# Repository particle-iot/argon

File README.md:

# Argon

<div align=center></div>

### Overview

The Argon is a powerful Wi-Fi enabled development board that can act as either a standalone Wi-Fi endpoint or Wi-Fi enabled gateway for Particle Mesh networks. It is based on the Nordic nRF52840 and has built-in battery charging circuitry so it’s easy to connect a Li-Po and deploy your local network in minutes.

The Argon is great for connecting existing projects to the Particle Device Cloud or as a gateway to connect an entire group of local endpoints.

### Features

* Espressif ESP32-D0WD 2.4Ghz Wi-Fi coprocessor 
  * On-board 4MB flash for ESP32 
  * 802.11 b/g/n support 
  * 802.11 n (2.4 GHz), up to 150 Mbps
* Nordic Semiconductor nRF52840 SoC 
  * ARM Cortex-M4F 32-bit processor @ 64MHz 
  * 1MB flash, 256KB RAM 
  * IEEE 802.15.4-2006: 250 Kbps 
  * Bluetooth 5: 2 Mbps, 1 Mbps, 500 Kbps, 125 Kbps 
  * Supports DSP instructions, HW accelerated Floating Point Unit (FPU) calculations 
  * ARM TrustZone CryptoCell-310 Cryptographic and security module 
  * Up to +8 dBm TX power (down to -20 dBm in 4 dB steps) 
  * NFC-A tag
* On-board additional 2MB SPI flash
* 20 mixed signal GPIO (6 x Analog, 8 x PWM), UART, I2C, SPI
* Micro USB 2.0 full speed (12 Mbps)
* Integrated Li-Po charging and battery connector
* JTAG (SWD) Connector
* RGB status LED
* Reset and Mode buttons
* On-board PCB antenna
* u.FL connector for external antenna
* Meets the Adafruit Feather [specification](https://learn.adafruit.com/adafruit-feather/feather-specification) in dimensions and pinout
* FCC, CE and IC certified
* RoHS compliant (lead-free)

### Structure of this repository:
 - /eagle
     + Contains the schematic and PCB files in the Eagle file format
 - /gerbers
     + Contains the manufacturing gerber files for the board
 - /datasheets
     + Contains the relevant datasheets of the components used on the Argon
 - /pdfs
     + Contains schematic files in PDF 

### Hardware datasheet

The complete datasheet for the Argon is available [here.](https://docs.particle.io/datasheets/wi-fi/argon-datasheet/)

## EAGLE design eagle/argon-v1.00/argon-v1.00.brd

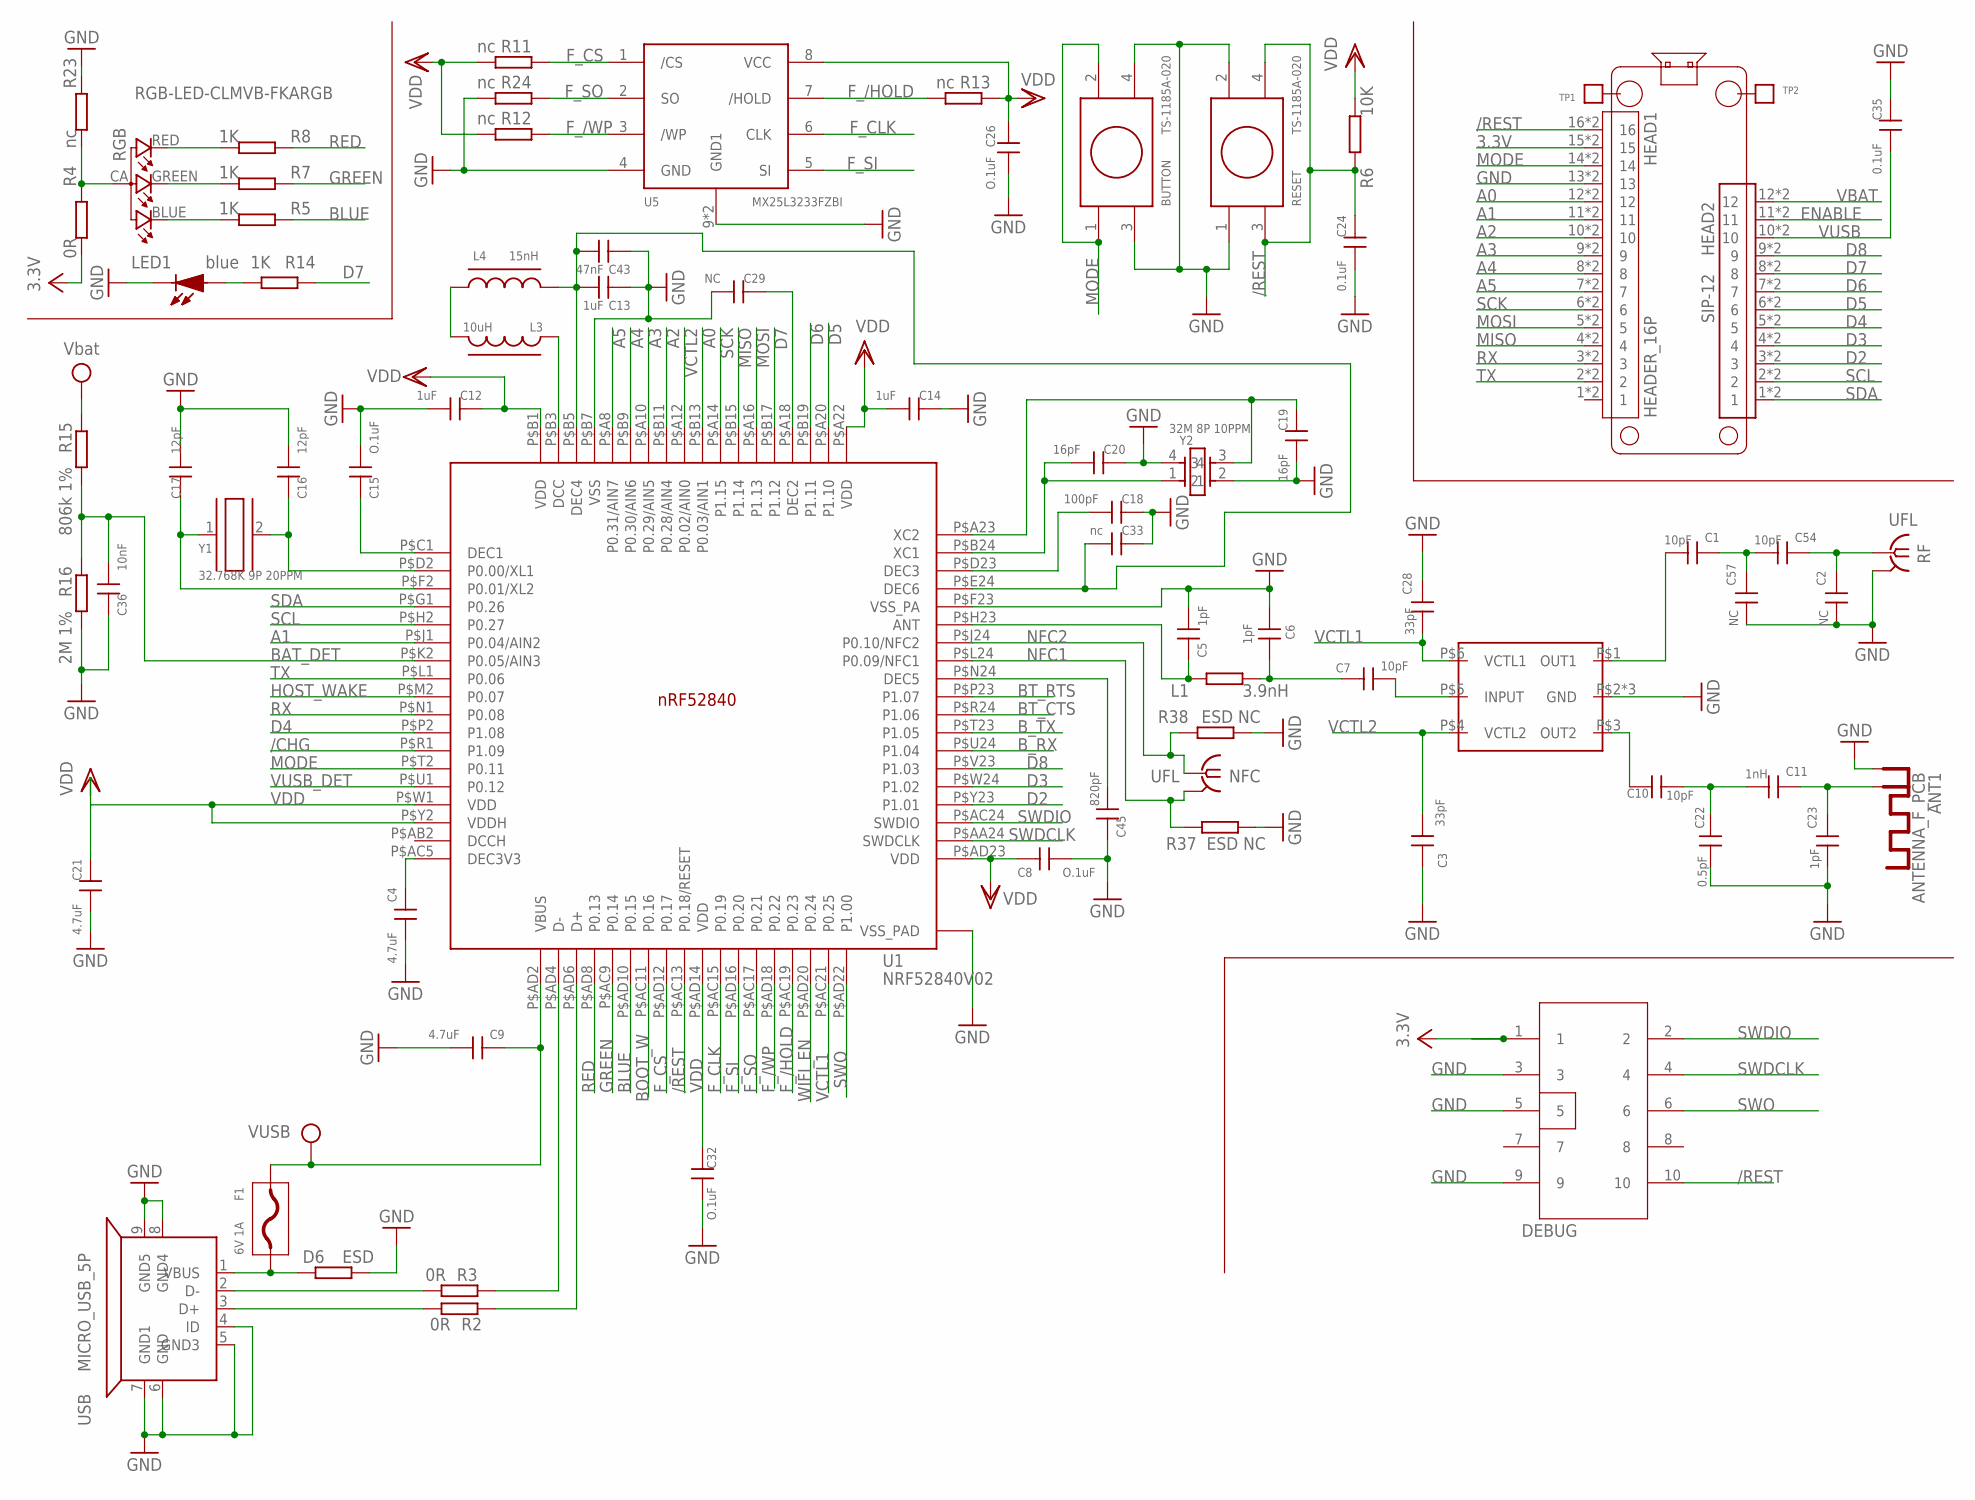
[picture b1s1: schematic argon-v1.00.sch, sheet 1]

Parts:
ANT1: ANTENNA_F_PCB
BUTTON: TS-1185A-020
C1, C7, C10, C54: 10pF; C-0402
C2, C29, C57: NC; C-0402
C3, C28: 33pF; C-0402
C4, C9, C21: 4.7uF; C-0402
C5, C6, C23: 1pF; C-0402
C8, C15, C26, C32: O.1uF; C-0402
C11: 1nH; C-0402
C12, C13, C14: 1uF; C-0402
C16, C17: 12pF; C-0402
C18: 100pF; C-0402
C19, C20: 16pF; C-0402
C22: 0.5pF; C-0402
C24, C35: 0.1uF; C-0402
C33: nc; C-0402
C36: 10nF; C-0402
C43: 47nF; C-0402
C45: 820pF; C-0402
D6: ESD; R-0402S
DEBUG: CON5X2; CON5X2_1.27
F1: 6V 1A; F0805
HEAD1: HEADER_16P; HEADER_16P2.54
HEAD2: SIP-12
L1: 3.9nH; R-0402S
L3: 10uH; R-0603A
L4: 15nH; R-0402S
LED1: blue; LED0603
NFC: UFL; IPEX-20279-001E
R2, R3, R4: 0R; R-0402S
R5, R7, R8, R14: 1K; R-0402S
R6: 10K; R-0402S
R11, R12, R13, R23, R24: nc; R-0402S
R15: 806k 1%; R-0402S
R16: 2M 1%; R-0402S
R37, R38: ESD NC; R-0402S
RESET: TS-1185A-020
RF: UFL; IPEX-20279-001E
RGB: RGB-LED-CLMVB-FKARGB; PLCC4-2MM-RGB
TP1, TP2: TPTP2.5; TP-2.5
U1: NRF52840V02; AQN507X7X0.85_HA-74_V2
U5: MX25L3233FZBI; USON8-3X4
U$2: SKY13351-378LF; MLPD-6-1X1
USB: MICRO_USB_5P; MICRO_USB
Y1: 32.768K 9P 20PPM; CRY_3215
Y2: 32M 8P 10PPM; CRY_2520

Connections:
3.3V: DEBUG.1, HEAD1.15, HEAD1.P$15 (15), R4.2; also elsewhere on the board
/CHG: U1.P$R1 (P1.09); also elsewhere on the board
/REST: C24.2, DEBUG.10, HEAD1.16, HEAD1.P$16 (16), R6.1, RESET.3, RESET.4, U1.P$AC13 (P0.18/RESET); also elsewhere on the board
A0: HEAD1.12, HEAD1.P$12 (12), U1.P$B13 (P0.03/AIN1)
A1: HEAD1.11, HEAD1.P$11 (11), U1.P$J1 (P0.04/AIN2)
A2: HEAD1.10, HEAD1.P$10 (10), U1.P$B11 (P0.28/AIN4)
A3: HEAD1.9, HEAD1.P$9 (9), U1.P$A10 (P0.29/AIN5)
A4: HEAD1.8, HEAD1.P$8 (8), U1.P$B9 (P0.30/AIN6)
A5: HEAD1.7, HEAD1.P$7 (7), U1.P$A8 (P0.31/AIN7)
BAT_DET: C36.1, R15.2, R16.1, U1.P$K2 (P0.05/AIN3)
BLUE: R5.1, U1.P$AD10 (P0.15)
BOOT_W: U1.P$AC11 (P0.16); also elsewhere on the board
BT_CTS: U1.P$R24 (P1.06); also elsewhere on the board
BT_RTS: U1.P$P23 (P1.07); also elsewhere on the board
B_RX: U1.P$U24 (P1.04); also elsewhere on the board
B_TX: U1.P$T23 (P1.05); also elsewhere on the board
D2: HEAD2.3, HEAD2.P$3 (3), U1.P$Y23 (P1.01)
D3: HEAD2.4, HEAD2.P$4 (4), U1.P$W24 (P1.02)
D4: HEAD2.5, HEAD2.P$5 (5), U1.P$P2 (P1.08)
D5: HEAD2.6, HEAD2.P$6 (6), U1.P$A20 (P1.10)
D6: HEAD2.7, HEAD2.P$7 (7), U1.P$B19 (P1.11)
D7: HEAD2.8, HEAD2.P$8 (8), R14.1, U1.P$B17 (P1.12)
D8: HEAD2.9, HEAD2.P$9 (9), U1.P$V23 (P1.03)
D+: R2.2, USB.3 (D+)
D-: R3.2, USB.2 (D-)
ENABLE: HEAD2.11, HEAD2.P$11 (11); also elsewhere on the board
F_/HOLD: R13.2, U1.P$AC19 (P0.23), U5.7 (/HOLD)
F_/WP: R12.1, U1.P$AD18 (P0.22), U5.3 (/WP)
F_CLK: U1.P$AC15 (P0.19), U5.6 (CLK)
F_CS: R11.1, U1.P$AD12 (P0.17), U5.1 (/CS)
F_SI: U1.P$AD16 (P0.20), U5.5 (SI)
F_SO: R24.1, U1.P$AC17 (P0.21), U5.2 (SO)
GND: ANT1.GND, BUTTON.3, BUTTON.4, C2.2, C3.1, C4.1, C5.1, C6.1, C8.1, C9.1, C12.1, C13.2, C14.2, C15.1, C16.1, C17.1, C18.2, C19.1, C20.2, C21.1, C22.2, C23.2, C24.1, C26.1, C28.1, C29.1, C32.1, C33.2, C35.2, C36.2, C43.2, C45.2, C57.2, D6.1, DEBUG.3, DEBUG.5, DEBUG.9, HEAD1.13, HEAD1.P$13 (13), LED1.2 (K), R16.2, R23.1, R24.2, R37.2, R38.1, RESET.1, RESET.2, RF.2@1 (GND), RF.2@2 (GND), U1.P$74 (VSS_PAD), U1.P$75 (VSS_PAD), U1.P$76 (VSS_PAD), U1.P$77 (VSS_PAD), U1.P$78 (VSS_PAD), U1.P$79 (VSS_PAD), U1.P$80 (VSS_PAD), U1.P$81 (VSS_PAD), U1.P$82 (VSS_PAD), U1.P$85 (VSS_PAD), U1.P$B7 (VSS), U1.P$F23 (VSS_PA), U5.4 (GND), U5.9 (GND1), U5.10 (GND1), U$2.P$2 (GND), U$2.P$7 (GND), U$2.P$8 (GND), USB.4 (ID), USB.5 (GND3), USB.6 (GND), USB.7 (GND1), USB.8 (GND4), USB.9 (GND5), Y2.2, Y2.4; also elsewhere on the board
GREEN: R7.1, U1.P$AC9 (P0.14)
HOST_WAKE: U1.P$M2 (P0.07); also elsewhere on the board
MISO: HEAD1.4, HEAD1.P$4 (4), U1.P$B15 (P1.14)
MODE: BUTTON.1, BUTTON.2, HEAD1.14, HEAD1.P$14 (14), U1.P$T2 (P0.11)
MOSI: HEAD1.5, HEAD1.P$5 (5), U1.P$A16 (P1.13)
unnamed: C5.2, L1.1, U1.P$H23 (ANT)
unnamed: C6.2, C7.2, L1.2
unnamed: C16.2, U1.P$D2 (P0.00/XL1), Y1.2
unnamed: C13.1, C33.1, C43.1, L4.2, U1.P$B5 (DEC4), U1.P$E24 (DEC6)
unnamed: L3.2, L4.1
unnamed: L3.1, U1.P$B3 (DCC)
unnamed: C15.2, U1.P$C1 (DEC1)
unnamed: C17.2, U1.P$F2 (P0.01/XL2), Y1.1
unnamed: C2.1, C54.1, RF.1
unnamed: C19.2, U1.P$A23 (XC2), Y2.3
unnamed: C18.1, U1.P$D23 (DEC3)
unnamed: C10.2, C11.2, C22.1
unnamed: C20.1, U1.P$B24 (XC1), Y2.1
unnamed: C7.1, U$2.P$5 (INPUT)
unnamed: C10.1, U$2.P$3 (OUT2)
unnamed: D6.2, F1.P$1 (1), USB.1 (VBUS)
unnamed: LED1.1 (A), R14.2
unnamed: R8.2, RGB.RED (4)
unnamed: R5.2, RGB.BLUE (2)
unnamed: R7.2, RGB.GREEN (3)
unnamed: C29.2, U1.P$A18 (DEC2)
unnamed: C4.2, U1.P$AC5 (DEC3V3)
unnamed: C45.1, U1.P$N24 (DEC5)
unnamed: C1.2, U$2.P$1 (OUT1)
unnamed: C1.1, C54.2, C57.1
unnamed: R4.1, R23.2, RGB.CA (1)
unnamed: R2.1, U1.P$AD6 (D+)
unnamed: R3.1, U1.P$AD4 (D-)
unnamed: ANT1.RF, C11.1, C23.1
NFC1: NFC.2@1 (GND), NFC.2@2 (GND), R37.1, U1.P$L24 (P0.09/NFC1)
NFC2: NFC.1, R38.2, U1.P$J24 (P0.10/NFC2)
RED: R8.1, U1.P$AD8 (P0.13)
RX: HEAD1.3, HEAD1.P$3 (3), U1.P$N1 (P0.08)
SCK: HEAD1.6, HEAD1.P$6 (6), U1.P$A14 (P1.15)
SCL: HEAD2.2, HEAD2.P$2 (2), U1.P$H2 (P0.27)
SDA: HEAD2.1, HEAD2.P$1 (1), U1.P$G1 (P0.26)
SWDCLK: DEBUG.4, U1.P$AA24 (SWDCLK)
SWDIO: DEBUG.2, U1.P$AC24 (SWDIO)
SWO: DEBUG.6, U1.P$AD22 (P1.00)
TX: HEAD1.2, HEAD1.P$2 (2), U1.P$L1 (P0.06)
VBAT: HEAD2.12, HEAD2.P$12 (12), R15.1; also elsewhere on the board
VCTL1: C28.2, U1.P$AC21 (P0.25), U$2.P$6 (VCTL1)
VCTL2: C3.2, U1.P$A12 (P0.02/AIN0), U$2.P$4 (VCTL2)
VDD: C8.2, C12.2, C14.1, C21.2, C26.2, C32.2, R6.2, R11.2, R12.2, R13.1, U1.P$A22 (VDD), U1.P$AD14 (VDD), U1.P$AD23 (VDD), U1.P$B1 (VDD), U1.P$W1 (VDD), U1.P$Y2 (VDDH), U5.8 (VCC); also elsewhere on the board
VUSB: C9.2, C35.1, F1.P$2 (2), HEAD2.10, HEAD2.P$10 (10), U1.P$AD2 (VBUS); also elsewhere on the board
VUSB_DET: U1.P$U1 (P0.12); also elsewhere on the board
WIFI_EN: U1.P$AD20 (P0.24); also elsewhere on the board

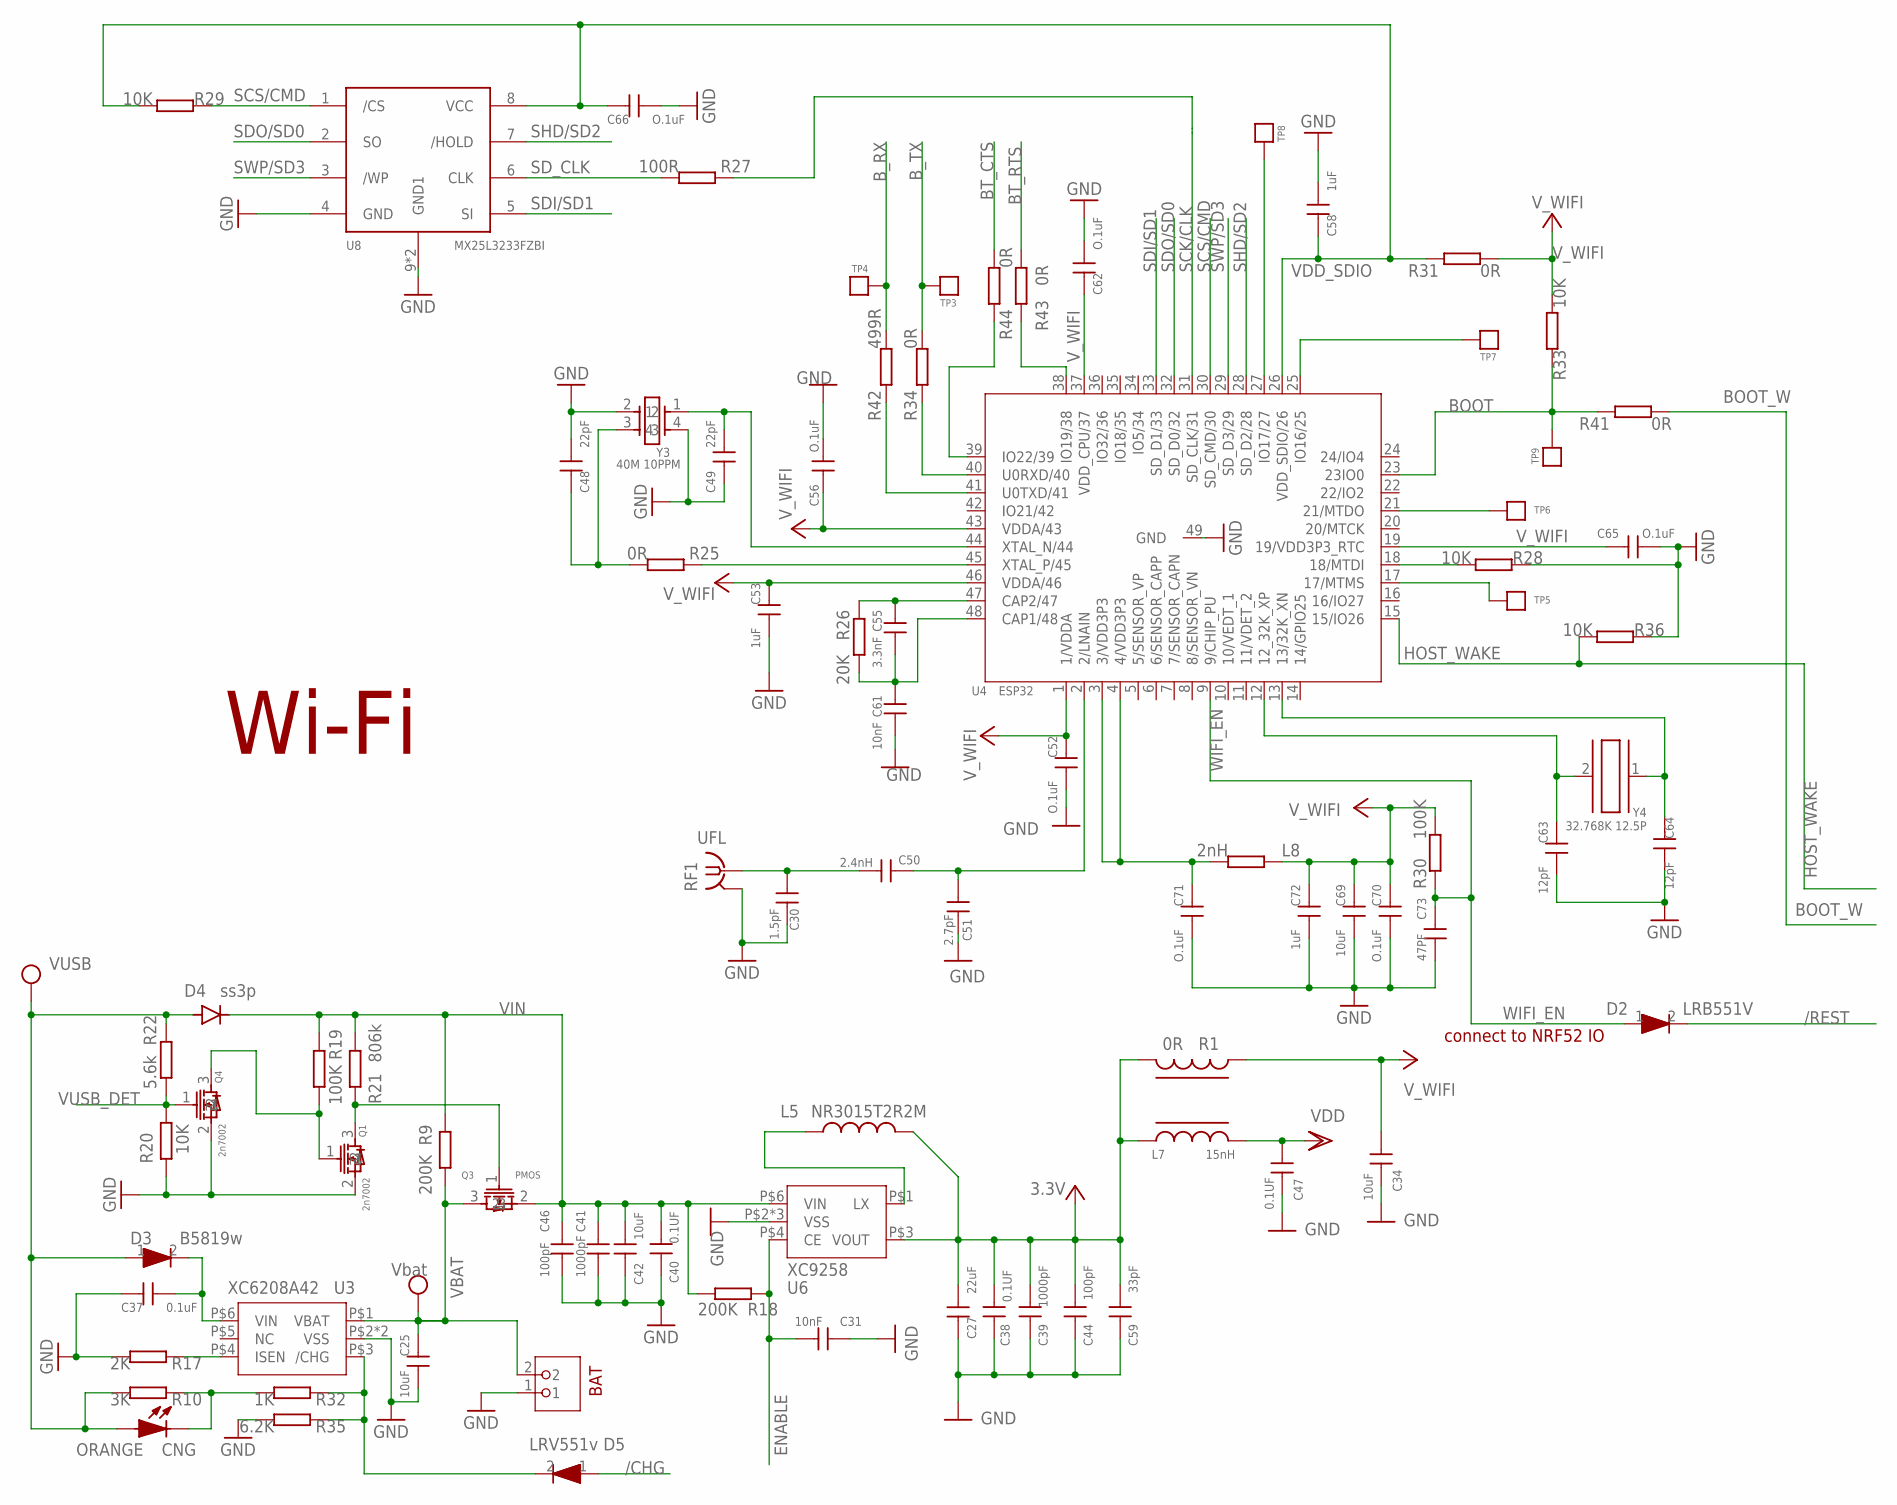
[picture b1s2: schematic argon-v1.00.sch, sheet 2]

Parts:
BAT: CON2P_SMT; CON_2.0MM_SMT
C25, C69: 10uF; C0805
C27: 22uF; C0805
C30: 1.5pF; C0201-N
C31: 10nF; C-0402
C34, C42: 10uF; C0603
C37: 0.1uF; C-0402
C38, C40, C47: 0.1UF; C-0402
C39, C41: 1000pF; C-0402
C44, C46: 100pF; C-0402
C48, C49: 22pF; C0201-N
C50: 2.4nH; C0201-N
C51: 2.7pF; C0201-N
C52, C56, C62, C65, C66, C70, C71: O.1uF; C-0402
C53, C58, C72: 1uF; C-0402
C55: 3.3nF; C0201-N
C59: 33pF; C-0402
C61: 10nF; C0201-N
C63, C64: 12pF; C-0402
C73: 47PF; C-0402
CNG: ORANGE; LED0603
D2: LRB551V; SOD-323
D3: B5819w; SOD-123
D4: ss3p; DIODE-DO-220AA(SMP)
D5: LRV551v; SOD-323
L5: NR3015T2R2M; INDUCTOR-NR3015
L7: 15nH; R-0402S
L8: 2nH; R-0402S
Q1, Q4: 2n7002; SOT323
Q3: PMOS; SOT-23
R1: 0R; R-0603A
R9, R18: 200K; R-0402S
R10: 3K; R-0402S
R17: 2K; R-0402S
R19, R30: 100K; R-0402S
R20, R28, R29, R33, R36: 10K; R-0402S
R21: 806k; R-0402S
R22: 5.6k; R-0402S
R25: 0R; R0201-N
R26: 20K; R0201-N
R27: 100R; R-0402S
R31, R34, R41, R43, R44: 0R; R-0402S
R32: 1K; R-0402S
R35: 6.2K; R-0402S
R42: 499R; R-0402S
RF1: UFL; IPEX-20279-001E
TP3, TP4, TP5, TP6, TP7, TP8, TP9: TP; TP0.7MM
U3: XC6208A42; USP-6C
U4: ESP32; QFN48-5X5
U6: XC9258; USP-6C
U8: MX25L3233FZBI; USON8-3X4
Y3: 40M 10PPM; CRY_2016
Y4: 32.768K 12.5P; CRY_3215

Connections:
3.3V: C27.1, C38.2, C39.2, C44.2, C59.2, L5.2, L7.1, R1.2, U6.P$3 (VOUT); also elsewhere on the board
/CHG: D5.1; also elsewhere on the board
/REST: D2.2; also elsewhere on the board
BOOT: R33.1, R41.1, TP9.P$1, U4.23 (23IO0)
BOOT_W: R41.2; also elsewhere on the board
BT_CTS: R44.2; also elsewhere on the board
BT_RTS: R43.2; also elsewhere on the board
B_RX: R42.2, TP4.P$1; also elsewhere on the board
B_TX: R34.2, TP3.P$1; also elsewhere on the board
CH: D5.2, R32.1, R35.1, U3.P$3 (/CHG)
ENABLE: C31.2, R18.1, U6.P$4 (CE); also elsewhere on the board
GND: BAT.1, C25.1, C27.2, C30.2, C31.1, C34.2, C37.2, C38.1, C39.1, C40.1, C41.2, C42.2, C44.1, C46.2, C47.2, C48.1, C49.2, C51.1, C52.1, C53.1, C56.1, C58.1, C59.1, C61.1, C62.1, C63.1, C64.1, C65.1, C66.1, C69.1, C70.1, C71.1, C72.1, C73.1, Q1.2, Q4.2, R17.2, R20.1, R28.1, R35.2, R36.1, RF1.2@1 (GND), RF1.2@2 (GND), U3.P$2 (VSS), U3.P$7 (VSS), U4.49 (GND), U6.P$2 (VSS), U6.P$5 (VSS), U6.P$7 (VSS), U8.4 (GND), U8.9 (GND1), U8.10 (GND1), Y3.2, Y3.4; also elsewhere on the board
HOST_WAKE: R36.2, U4.15 (15/IO26); also elsewhere on the board
unnamed: C49.1, U4.44 (XTAL_N/44), Y3.1
unnamed: Q1.1, Q4.3, R19.1
unnamed: R25.1, U4.45 (XTAL_P/45)
unnamed: Q1.3, Q3.1, R21.2
unnamed: TP8.P$1, U4.27 (IO17/27)
unnamed: C55.2, R26.1, U4.47 (CAP2/47)
unnamed: R34.1, U4.40 (U0RXD/40)
unnamed: R17.1, U3.P$4 (ISEN)
unnamed: C30.1, C50.2, RF1.1
unnamed: R42.1, U4.41 (U0TXD/41)
unnamed: CNG.2 (K), R10.1, R32.2
unnamed: R44.1, U4.39 (IO22/39)
unnamed: L5.1, U6.P$1 (LX)
unnamed: C55.1, C61.2, R26.2, U4.48 (CAP1/48)
unnamed: C37.1, D3.2, U3.P$6 (VIN)
unnamed: C71.2, L8.2, U4.3 (3/VDD3P3), U4.4 (4/VDD3P3)
unnamed: TP7.P$1, U4.25 (IO16/25)
unnamed: R28.2, U4.18 (18/MTDI)
unnamed: C63.2, U4.12 (12_32K_XP), Y4.2
unnamed: C64.2, U4.13 (13/32K_XN), Y4.1
unnamed: C48.2, R25.2, Y3.3
unnamed: TP6.P$1, U4.21 (21/MTDO)
unnamed: C50.1, C51.2, U4.2 (2/LNAIN)
unnamed: TP5.P$1, U4.17 (17/MTMS)
unnamed: R43.1, U4.38 (IO19/38)
SCK/CLK: R27.1, U4.31 (SD_CLK/31)
SCS/CMD: R29.1, U4.30 (SD_CMD/30), U8.1 (/CS)
SDI/SD1: U4.33 (SD_D1/33), U8.5 (SI)
SDO/SD0: U4.32 (SD_D0/32), U8.2 (SO)
SD_CLK: R27.2, U8.6 (CLK)
SHD/SD2: U4.28 (SD_D2/28), U8.7 (/HOLD)
SWP/SD3: U4.29 (SD_D3/29), U8.3 (/WP)
VBAT: BAT.2, C25.2, Q3.3, R9.1, U3.P$1 (VBAT); also elsewhere on the board
VDD: C47.1, L7.2; also elsewhere on the board
VDD_SDIO: C58.2, C66.2, R29.2, R31.1, U4.26 (VDD_SDIO/26), U8.8 (VCC)
VIN: C40.2, C41.1, C42.1, C46.1, D4.CATHODE, Q3.2, R9.2, R18.2, R19.2, R21.1, U6.P$6 (VIN)
VUSB: CNG.1 (A), D3.1, D4.ANODE, R10.2, R22.1; also elsewhere on the board
VUSB_DET: Q4.1, R20.2, R22.2; also elsewhere on the board
V_WIFI: C34.1, C52.2, C53.2, C56.2, C62.2, C65.2, C69.2, C70.2, C72.2, L8.1, R1.1, R30.2, R31.2, R33.2, U4.1 (1/VDDA), U4.19 (19/VDD3P3_RTC), U4.37 (VDD_CPU/37), U4.43 (VDDA/43), U4.46 (VDDA/46)
WIFI_EN: C73.2, D2.1, R30.1, U4.9 (9/CHIP_PU); also elsewhere on the board

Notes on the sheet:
Wi-Fi
BAT
connect to NRF52 IO

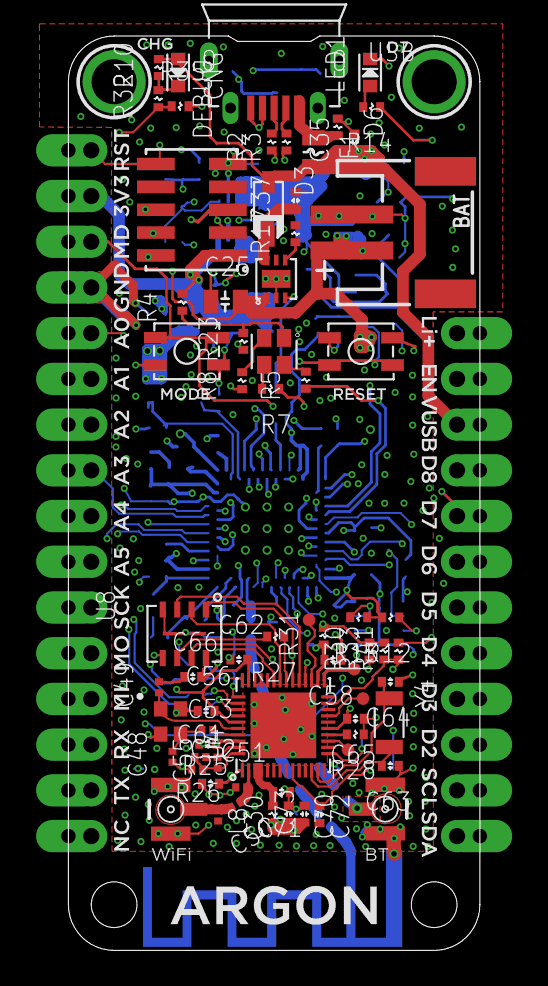
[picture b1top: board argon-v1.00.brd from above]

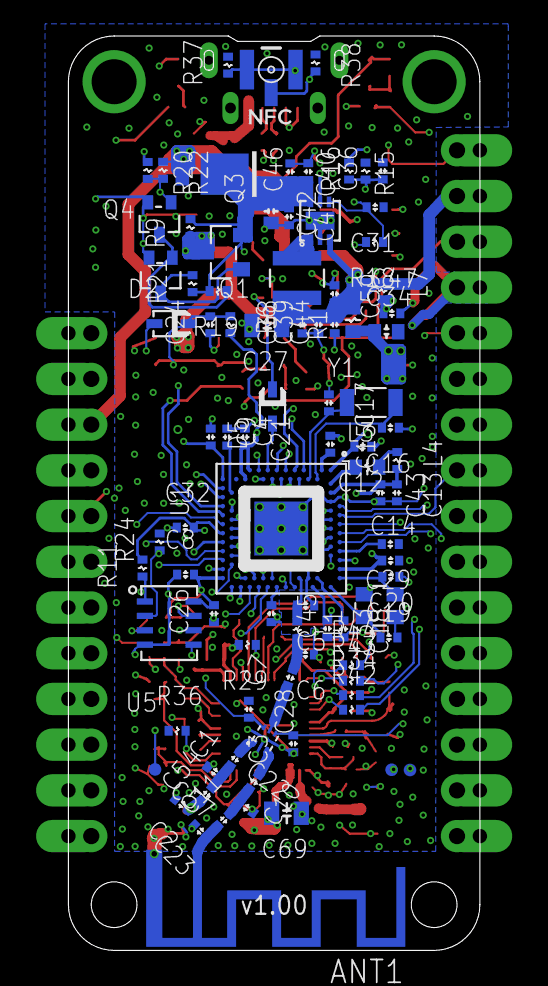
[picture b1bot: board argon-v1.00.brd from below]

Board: 6 copper layers, 22.9 x 50.8 mm, 161 parts (89 on the bottom side), 122 nets.

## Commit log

2018-10-03 added design files
2018-10-30 Fix bullets. Silly GFM.
2019-03-04 Include MX25L3233F SPI flash datasheet
